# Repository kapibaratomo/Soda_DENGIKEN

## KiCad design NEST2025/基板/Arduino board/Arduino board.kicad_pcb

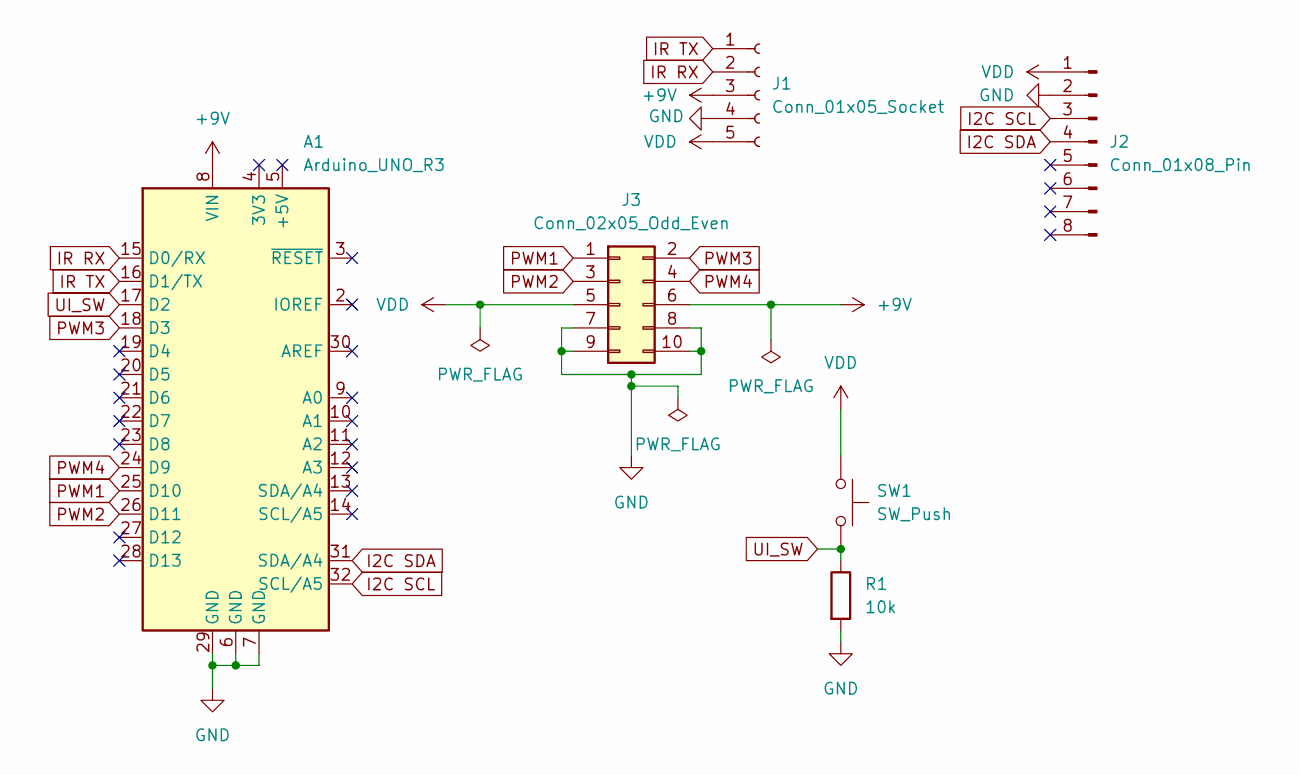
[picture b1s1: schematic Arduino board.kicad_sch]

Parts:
A1: Arduino_UNO_R3
J1: Conn_01x05_Socket; JST_XH_B5B-XH-A_1x05_P2.50mm_Vertical
J2: Conn_01x08_Pin; PinSocket_1x08_P2.54mm_Vertical
J3: Conn_02x05_Odd_Even; IDC-Header_2x05_P2.54mm_Vertical
R1: 10k; R_0603_1608Metric
SW1: SW_Push; TVGP01-G73BB

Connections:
+9V: A1.8 (VIN), J1.3, J3.6
GND: A1.6 (GND), A1.7 (GND), A1.29 (GND), J1.4, J2.2, J3.7, J3.8, J3.9, J3.10, R1.2
I2C SCL: A1.32 (SCL/A5), J2.3
I2C SDA: A1.31 (SDA/A4), J2.4
IR RX: A1.15 (D0/RX), J1.2
IR TX: A1.16 (D1/TX), J1.1
PWM1: A1.25 (D10), J3.1
PWM2: A1.26 (D11), J3.3
PWM3: A1.18 (D3), J3.2
PWM4: A1.24 (D9), J3.4
UI_SW: A1.17 (D2), R1.1, SW1.2
VDD: J1.5, J2.1, J3.5, SW1.1

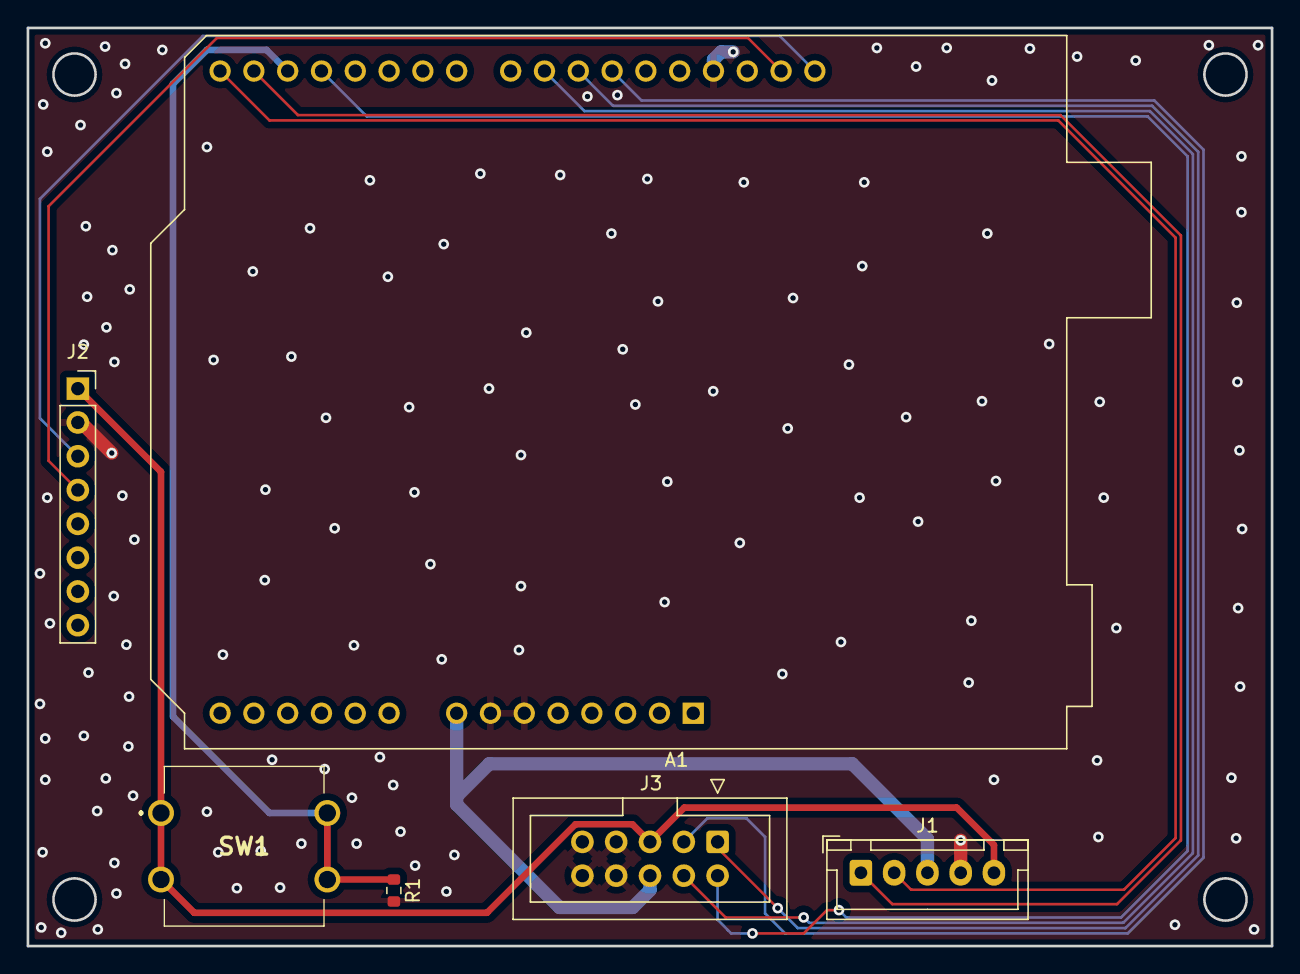
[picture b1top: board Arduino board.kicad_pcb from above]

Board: 2 copper layers, 93.5 x 69.0 mm, 6 parts (0 on the bottom side), 12 nets.

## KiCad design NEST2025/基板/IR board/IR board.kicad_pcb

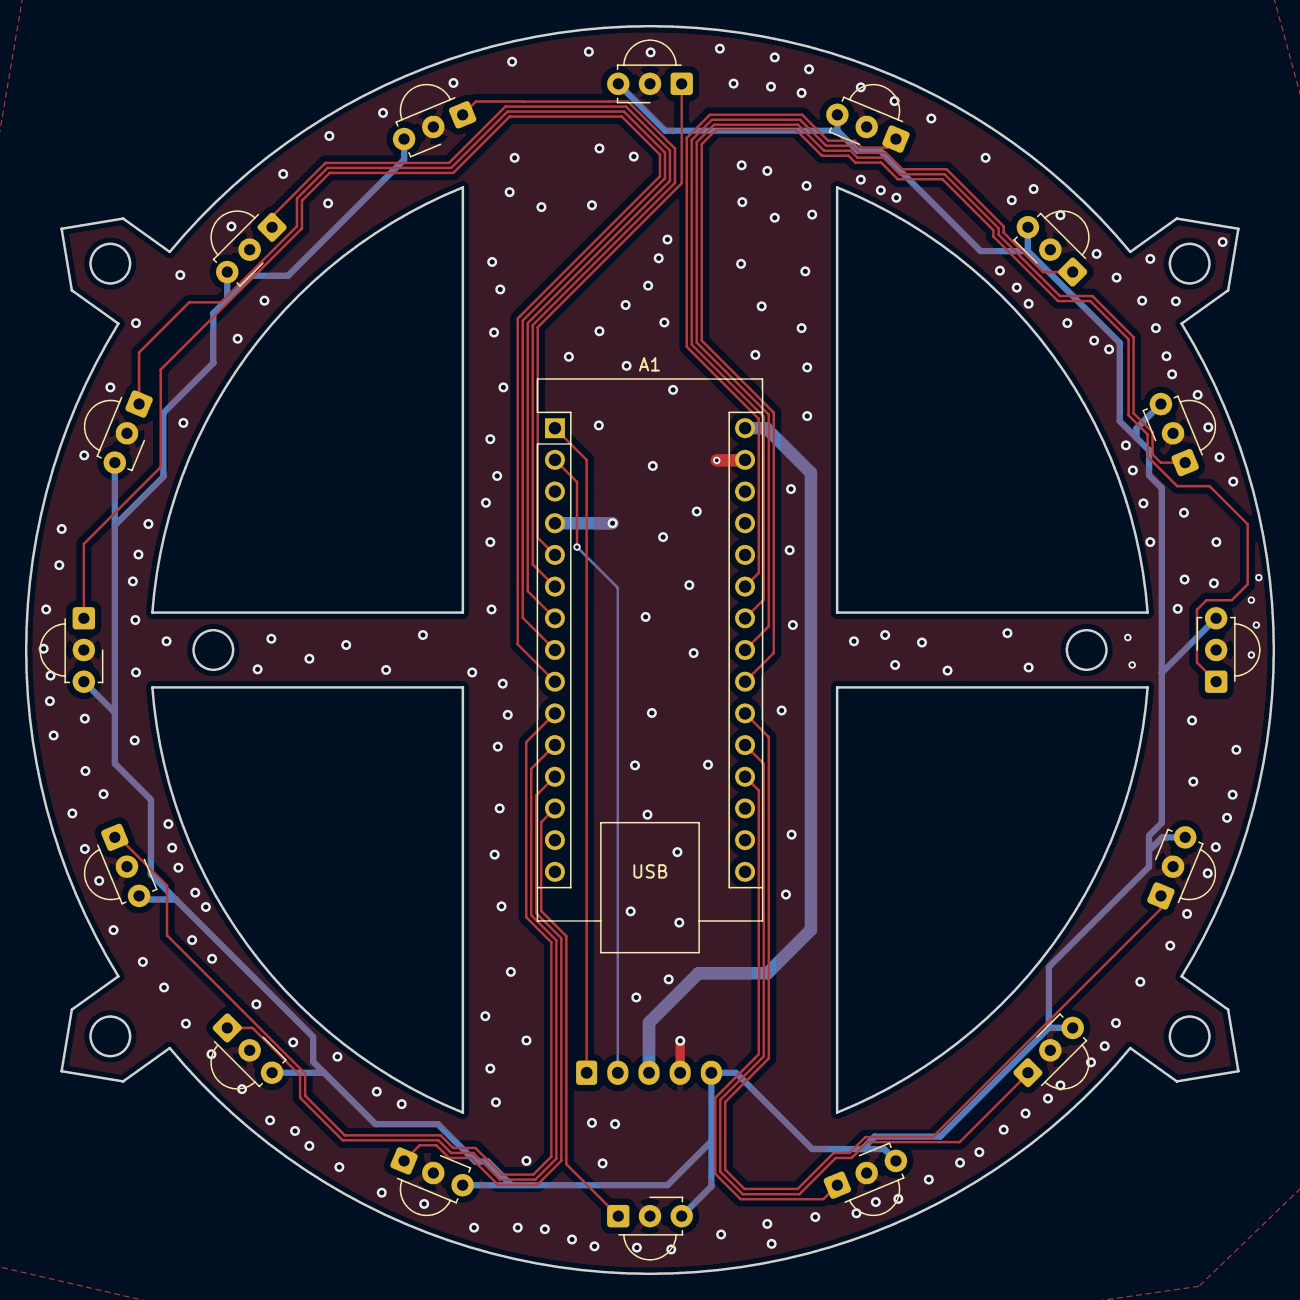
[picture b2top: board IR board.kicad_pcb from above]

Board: 2 copper layers, 100.0 x 100.0 mm, 18 parts (1 on the bottom side), 21 nets.

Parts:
A1: Arduino_Nano_Every; Arduino_Nano
J1: Conn_01x05_Socket; JST_XH_B5B-XH-A_1x05_P2.50mm_Vertical
U1, U2, U3, U4, U5, U6, U7, U8, U9, U10, U11, U12, U13, U14, U15, U16: TSSP58038; Vishay_MINICAST-3Pin

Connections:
+3.3V: J1.5, U1.3 (Vs), U2.3 (Vs), U3.3 (Vs), U4.3 (Vs), U5.3 (Vs), U6.3 (Vs), U7.3 (Vs), U8.3 (Vs), U9.3 (Vs), U10.3 (Vs), U11.3 (Vs), U12.3 (Vs), U13.3 (Vs), U14.3 (Vs), U15.3 (Vs), U16.3 (Vs)
+9V: A1.30 (VIN), J1.3
GND: A1.4 (GND), A1.29 (GND), J1.4, U1.2 (GND), U2.2 (GND), U3.2 (GND), U4.2 (GND), U5.2 (GND), U6.2 (GND), U7.2 (GND), U8.2 (GND), U9.2 (GND), U10.2 (GND), U11.2 (GND), U12.2 (GND), U13.2 (GND), U14.2 (GND), U15.2 (GND), U16.2 (GND)
IR 0: A1.5 (D2), U1.1 (OUT)
IR 1: A1.6 (D3), U2.1 (OUT)
IR 2: A1.7 (D4), U3.1 (OUT)
IR 3: A1.8 (D5), U4.1 (OUT)
IR 4: A1.9 (D6), U5.1 (OUT)
IR 5: A1.10 (D7), U6.1 (OUT)
IR 6: A1.11 (D8), U7.1 (OUT)
IR 7: A1.12 (D9), U8.1 (OUT)
IR 8: A1.13 (D10), U9.1 (OUT)
IR 9: A1.19 (A0), U10.1 (OUT)
IR 10: A1.20 (A1), U11.1 (OUT)
IR 11: A1.21 (A2), U12.1 (OUT)
IR 12: A1.22 (A3), U13.1 (OUT)
IR 13: A1.23 (SDA/A4), U14.1 (OUT)
IR 14: A1.24 (SCL/A5), U15.1 (OUT)
IR 15: A1.25 (A6), U16.1 (OUT)
IR RX: A1.2 (RX1), J1.2
IR TX: A1.1 (TX1), J1.1

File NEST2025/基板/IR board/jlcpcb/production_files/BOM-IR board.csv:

Comment,Designator,Footprint,LCSC,Quantity
TSSP58038,U15,Vishay_MINICAST-3Pin,,1
TSSP58038,U9,Vishay_MINICAST-3Pin,,1
TSSP58038,U13,Vishay_MINICAST-3Pin,,1
TSSP58038,U5,Vishay_MINICAST-3Pin,,1
TSSP58038,U8,Vishay_MINICAST-3Pin,,1
TSSP58038,U6,Vishay_MINICAST-3Pin,,1
TSSP58038,U14,Vishay_MINICAST-3Pin,,1
TSSP58038,U16,Vishay_MINICAST-3Pin,,1
TSSP58038,U1,Vishay_MINICAST-3Pin,,1
TSSP58038,U12,Vishay_MINICAST-3Pin,,1
TSSP58038,U10,Vishay_MINICAST-3Pin,,1
TSSP58038,U11,Vishay_MINICAST-3Pin,,1
TSSP58038,U2,Vishay_MINICAST-3Pin,,1
TSSP58038,U7,Vishay_MINICAST-3Pin,,1
TSSP58038,U4,Vishay_MINICAST-3Pin,,1
Arduino_Nano_Every,A1,Arduino_Nano,,1
TSSP58038,U3,Vishay_MINICAST-3Pin,,1
Conn_01x05_Socket,J1,JST_XH_B5B-XH-A_1x05_P2.50mm_Vertical,,1

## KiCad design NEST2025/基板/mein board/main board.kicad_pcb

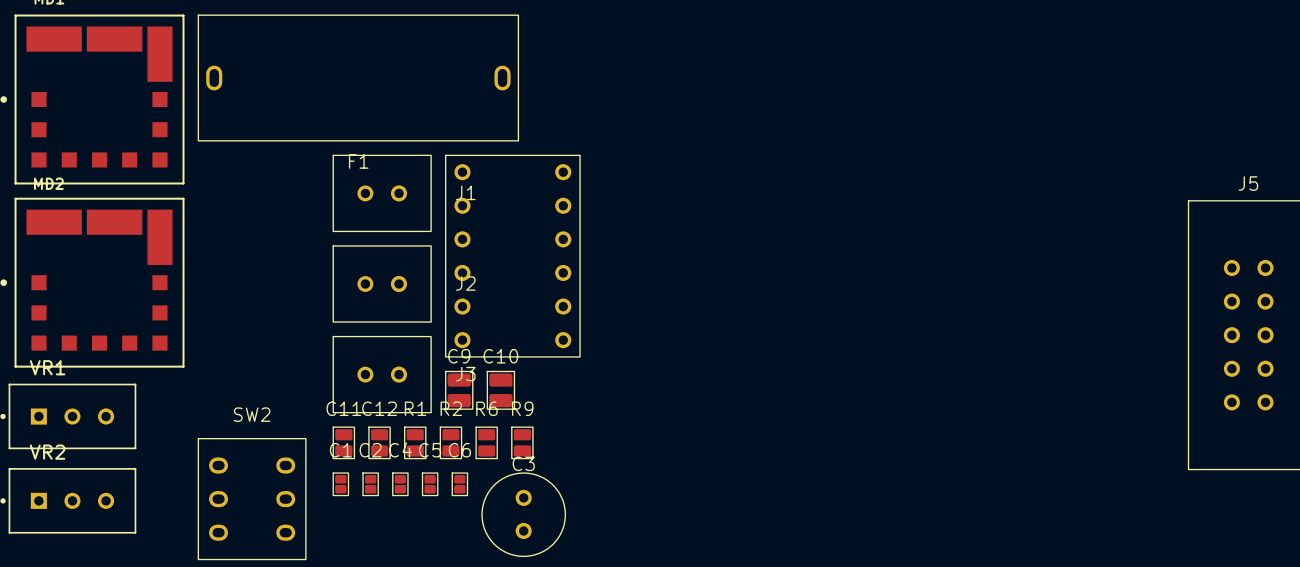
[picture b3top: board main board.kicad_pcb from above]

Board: 2 copper layers, 25 parts (0 on the bottom side), 19 nets, no tracks yet.

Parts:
C1, C2, C4, C6: 0.1; chip 1005
C3: 100; OS-CON 100μF
C5: 1; chip 1005
C9, C10: 22; chip 2012
C11, C12: 10; chip 1608
F1: Fuse
J1, J2, J3: Conn_01x02_Socket; XHConn_01×02_Socket
J5: Conn_02x05_Odd_Even; Box header 10P
MD1: OKL-T_3-W5N-C; OKL-T-3-W5N-C_0
MD2: OKL-T_6-W12N-C; OKL-T-6-W12N-C_0
R1, R2, R6, R9: 1.2k; chip 1608
SW2: SW_Push_DPDT; 6P toggle switch
U1: DRV8835
VR1, VR2: 3296W-1-203LF

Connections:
+3.3V: C11.1, C12.1, J5.5, MD1.4 (VOUT), MD1.5 (SENSE), MD2.4 (VOUT), MD2.5 (SENSE), R1.1, R9.1
+5V: C5.1, C6.1, J5.6, U1.7 (VDD)
+9V: C3.2, C4.2, C9.1, C10.1, MD1.2 (VIN), MD2.2 (VIN), SW2.1 (A), SW2.4 (A), U1.1 (VM)
AOUT1: C1.1, J1.1, U1.2 (AOUT1)
AOUT2: C1.2, J1.2, U1.3 (AOUT2)
BOUT1: C2.1, J2.1, U1.4 (BOUT1)
BOUT2: C2.2, J2.2, U1.5 (BOUT2)
GND: C3.1, C4.1, C9.2, C10.2, C11.2, C12.2, J3.1, J5.7, J5.8, J5.9, J5.10, MD1.1 (~ON/OFF_CONTROL), MD1.3 (1_GROUND), MD1.7 (2_GROUND), MD2.1 (~ON/OFF_CONTROL), MD2.3 (1_GROUND), MD2.7 (2_GROUND), R1.2, R2.2, R6.2, R9.2, U1.6 (GND)
unnamed: F1.2, SW2.2 (B), SW2.5 (B)
unnamed: F1.1, J3.2
unnamed: MD1.6 (TRIM), VR1.1
unnamed: MD2.6 (TRIM), VR2.1
unnamed: R2.1, VR2.2, VR2.3
unnamed: R6.1, VR1.2, VR1.3
unnamed: C5.2, C6.2, U1.8 (MODE)
PWM1: J5.1, U1.9 (AIN1)
PWM2: J5.3, U1.10 (AIN2)
PWM3: J5.2, U1.11 (BIN1)
PWM4: J5.4, U1.12 (BIN2)

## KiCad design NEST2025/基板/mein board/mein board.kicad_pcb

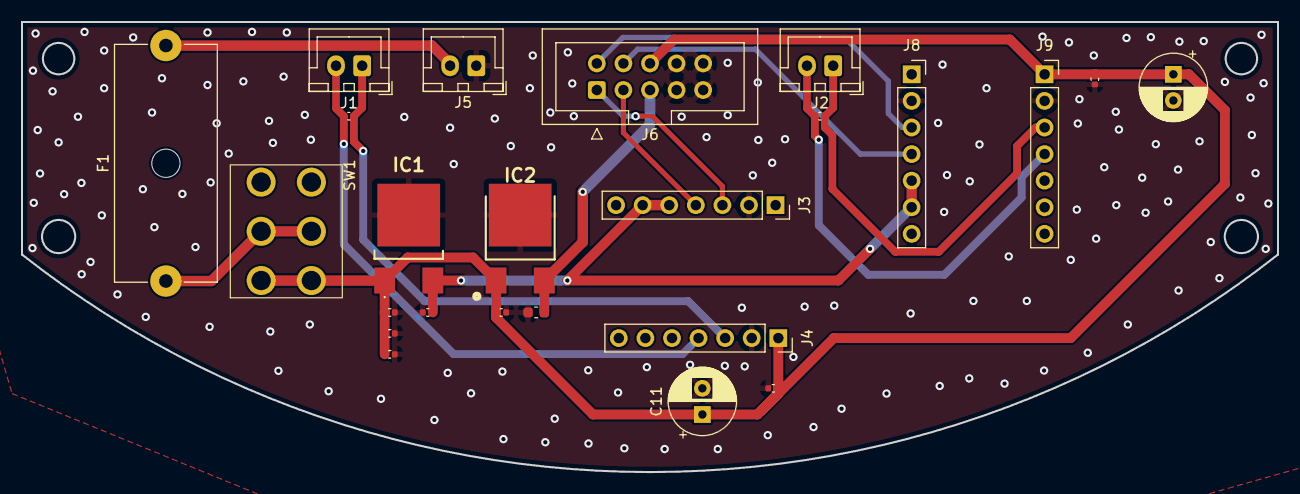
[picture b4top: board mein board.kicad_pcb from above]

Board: 2 copper layers, 120.0 x 43.0 mm, 24 parts (0 on the bottom side), 14 nets.

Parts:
C1, C2, C3, C4, C5: 0.1uF; C_0402_1005Metric
C6: 10uF; C_0603_1608Metric
C7, C8, C10, C12: 0.1; C_0402_1005Metric
C9, C11: 100; CP_Radial_D6.3mm_P2.50mm
F1: Fuse; Fuseholder_Cylinder-5x20mm_Schurter_0031_8201_Horizontal_Op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
IC1: NJM7805SDL1-TE1; NJM7805SDL1TE1
IC2: NJM2391DL1-33-TE1
J1, J2, J5: Conn_01x02_Socket; JST_XH_B2B-XH-A_1x02_P2.50mm_Vertical
J3, J4, J8, J9: Conn_01x07_Pin; PinSocket_1x07_P2.54mm_Vertical
J6: Conn_02x05_Odd_Even; IDC-Header_2x05_P2.54mm_Vertical
SW1: SW_Push_DPDT; Toggle

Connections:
+3.3V: C6.1, IC2.2 (VOUT), J6.5
+5V: C4.1, IC1.3 (VOUT), J3.5, J3.6, J8.5, J8.6
+9V: C1.1, C2.1, C3.1, C5.1, C9.1, C10.1, C11.1, C12.1, IC1.1 (VIN), IC2.1 (VIN), J4.1, J6.6, J9.1, SW1.1 (A), SW1.4 (A)
AOUT1: C7.1, J1.1, J4.3
AOUT2: C7.2, J1.2, J4.4
BOUT1: C8.1, J2.1, J9.3
BOUT2: C8.2, J2.2, J9.4
GND: C1.2, C2.2, C3.2, C4.2, C5.2, C6.2, C9.2, C10.2, C11.2, C12.2, IC1.2 (GND), IC2.3 (GND), J3.2, J4.2, J5.1, J6.7, J6.8, J6.9, J6.10, J8.2, J9.2
unnamed: F1.2, SW1.2 (B), SW1.5 (B)
unnamed: F1.1, J5.2
PWM1: J3.3, J6.1
PWM2: J3.4, J6.3
PWM3: J6.2, J8.3
PWM4: J6.4, J8.4

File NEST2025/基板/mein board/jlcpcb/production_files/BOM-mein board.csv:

Comment,Designator,Footprint,LCSC,Quantity
0.1uF,C3,C_0402_1005Metric,,1
0.1uF,C4,C_0402_1005Metric,,1
Fuse,F1,Fuseholder_Cylinder-5x20mm_Schurter_0031_8201_Horizontal_Open,,1
0.1uF,C2,C_0402_1005Metric,,1
0.1,C7,C_0402_1005Metric,,1
0.1,C10,C_0402_1005Metric,,1
Conn_01x07_Pin,J4,PinSocket_1x07_P2.54mm_Vertical,,1
Conn_01x02_Socket,J1,JST_XH_B2B-XH-A_1x02_P2.50mm_Vertical,,1
Conn_01x07_Pin,J3,PinSocket_1x07_P2.54mm_Vertical,,1
10uF,C6,C_0603_1608Metric,,1
100,C9,CP_Radial_D6.3mm_P2.50mm,,1
0.1uF,C5,C_0402_1005Metric,,1
100,C11,CP_Radial_D6.3mm_P2.50mm,,1
Conn_01x02_Socket,J2,JST_XH_B2B-XH-A_1x02_P2.50mm_Vertical,,1
0.1uF,C1,C_0402_1005Metric,,1
NJM2391DL1-33-TE1,IC2,NJM2391DL1-33-TE1,,1
SW_Push_DPDT,SW1,Toggle,,1
0.1,C12,C_0402_1005Metric,,1
NJM7805SDL1-TE1,IC1,NJM7805SDL1TE1,,1
0.1,C8,C_0402_1005Metric,,1
Conn_02x05_Odd_Even,J6,IDC-Header_2x05_P2.54mm_Vertical,,1
Conn_01x07_Pin,J9,PinSocket_1x07_P2.54mm_Vertical,,1
Conn_01x02_Socket,J5,JST_XH_B2B-XH-A_1x02_P2.50mm_Vertical,,1
Conn_01x07_Pin,J8,PinSocket_1x07_P2.54mm_Vertical,,1

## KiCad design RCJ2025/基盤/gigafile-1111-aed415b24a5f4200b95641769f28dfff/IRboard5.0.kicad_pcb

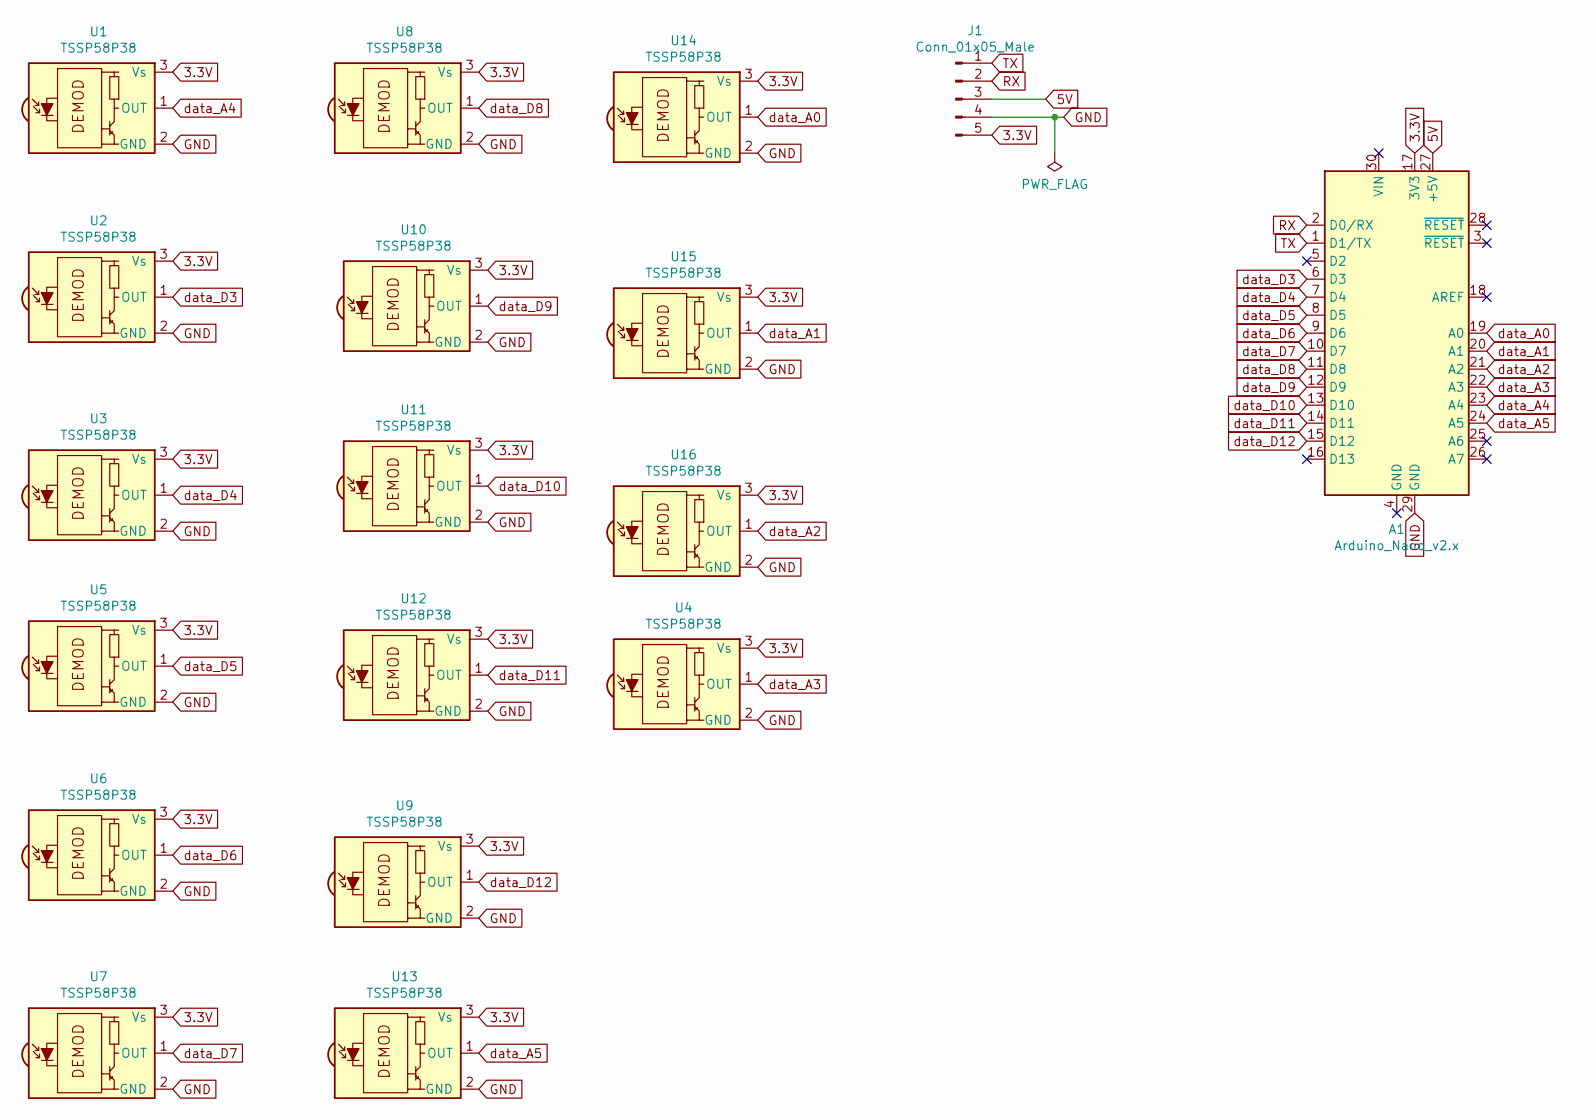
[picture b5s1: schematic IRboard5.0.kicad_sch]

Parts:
A1: Arduino_Nano_v2.x; Arduino_Nano
J1: Conn_01x05_Male; JST_XH_B5B-XH-A_1x05_P2.50mm_Vertical
U1, U2, U3, U4, U5, U6, U7, U8, U9, U10, U11, U12, U13, U14, U15, U16: TSSP58P38; Vishay_MINICAST-3Pin

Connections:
3.3V: A1.17 (3V3), J1.5, U1.3 (Vs), U2.3 (Vs), U3.3 (Vs), U4.3 (Vs), U5.3 (Vs), U6.3 (Vs), U7.3 (Vs), U8.3 (Vs), U9.3 (Vs), U10.3 (Vs), U11.3 (Vs), U12.3 (Vs), U13.3 (Vs), U14.3 (Vs), U15.3 (Vs), U16.3 (Vs)
5V: A1.27 (+5V), J1.3
GND: A1.29 (GND), J1.4, U1.2 (GND), U2.2 (GND), U3.2 (GND), U4.2 (GND), U5.2 (GND), U6.2 (GND), U7.2 (GND), U8.2 (GND), U9.2 (GND), U10.2 (GND), U11.2 (GND), U12.2 (GND), U13.2 (GND), U14.2 (GND), U15.2 (GND), U16.2 (GND)
RX: A1.2 (D0/RX), J1.2
TX: A1.1 (D1/TX), J1.1
data_A0: A1.19 (A0), U14.1 (OUT)
data_A1: A1.20 (A1), U15.1 (OUT)
data_A2: A1.21 (A2), U16.1 (OUT)
data_A3: A1.22 (A3), U4.1 (OUT)
data_A4: A1.23 (A4), U1.1 (OUT)
data_A5: A1.24 (A5), U13.1 (OUT)
data_D3: A1.6 (D3), U2.1 (OUT)
data_D4: A1.7 (D4), U3.1 (OUT)
data_D5: A1.8 (D5), U5.1 (OUT)
data_D6: A1.9 (D6), U6.1 (OUT)
data_D7: A1.10 (D7), U7.1 (OUT)
data_D8: A1.11 (D8), U8.1 (OUT)
data_D9: A1.12 (D9), U10.1 (OUT)
data_D10: A1.13 (D10), U11.1 (OUT)
data_D11: A1.14 (D11), U12.1 (OUT)
data_D12: A1.15 (D12), U9.1 (OUT)

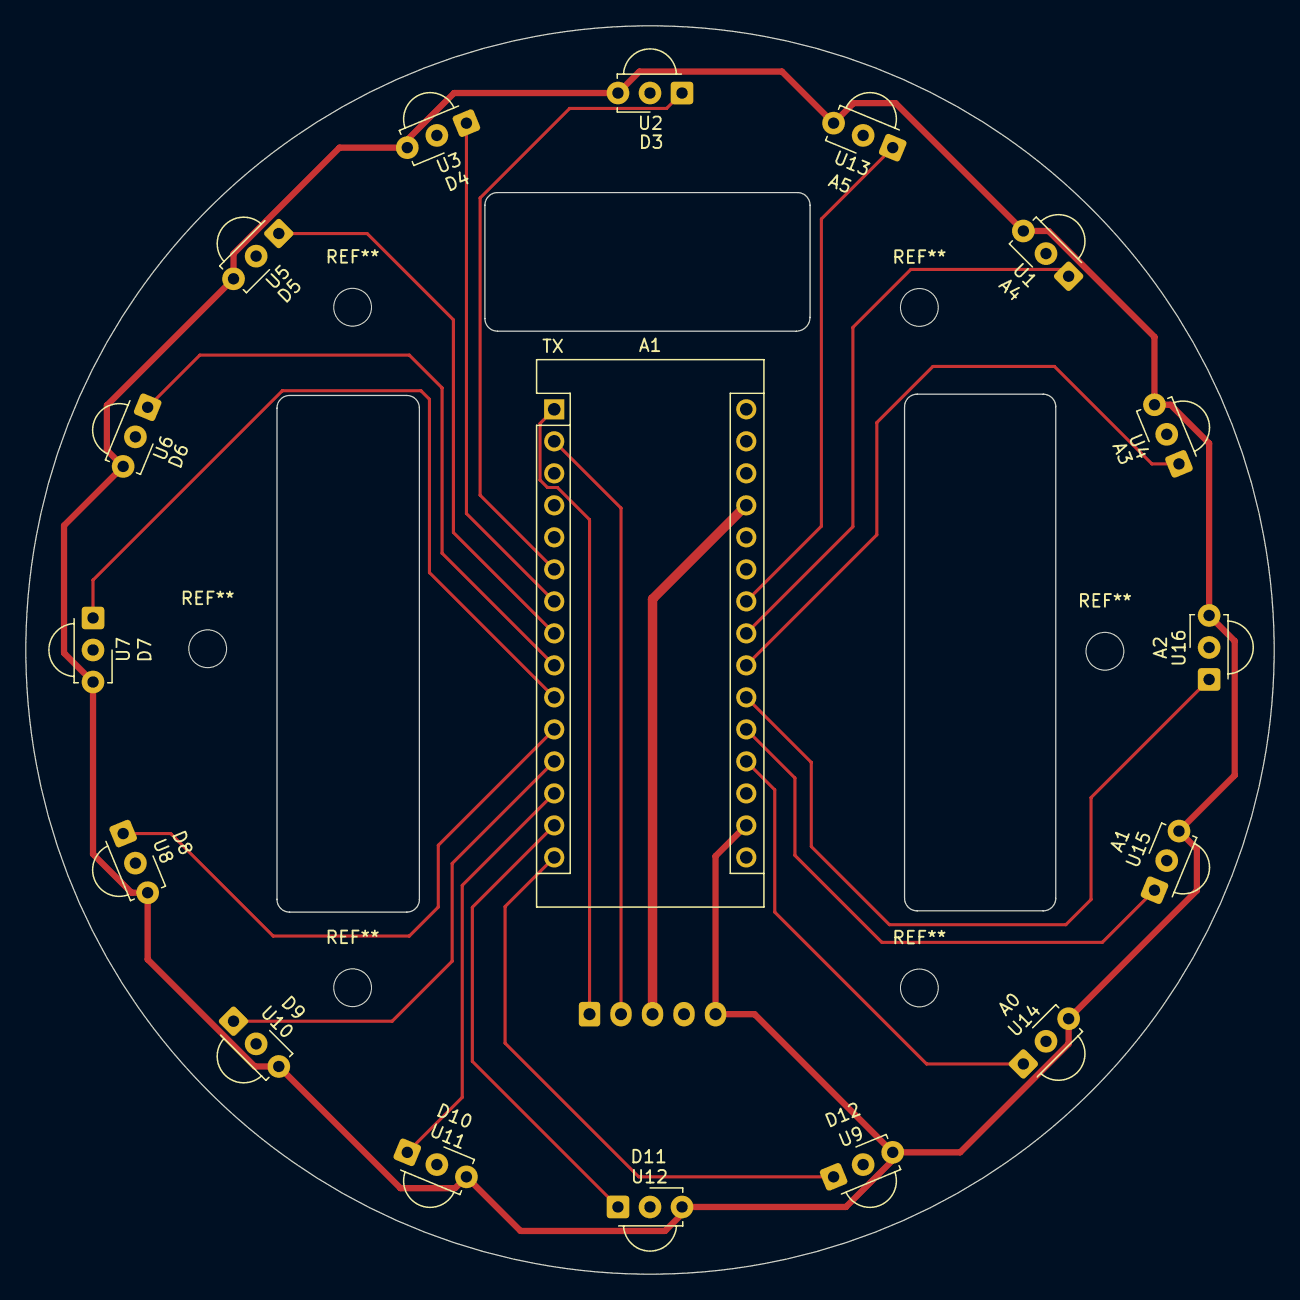
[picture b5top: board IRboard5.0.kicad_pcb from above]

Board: 2 copper layers, 99.1 x 99.1 mm, 18 parts (1 on the bottom side), 21 nets.

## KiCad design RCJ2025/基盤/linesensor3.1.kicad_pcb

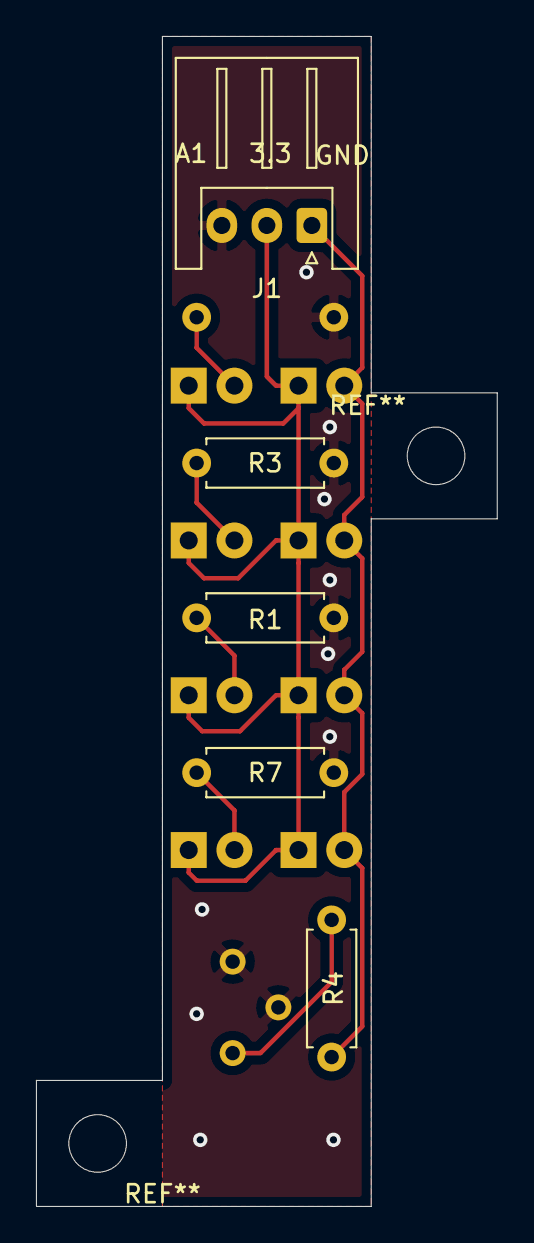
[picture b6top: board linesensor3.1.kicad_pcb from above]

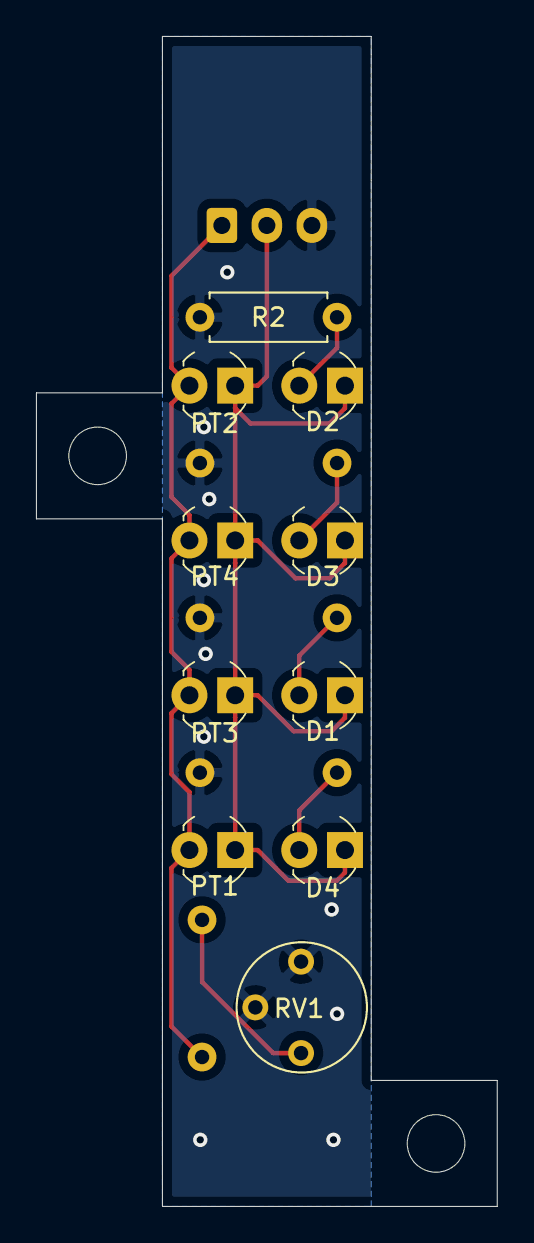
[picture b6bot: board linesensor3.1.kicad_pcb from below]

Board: 2 copper layers, 25.6 x 65.0 mm, 15 parts (10 on the bottom side), 8 nets.

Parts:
D1, D2, D3, D4: LED; LED_3mm_Radial
J1: Conn_01x03_Female; JST_XH_S3B-XH-A_1x03_P2.50mm_Horizontal
PT1, PT2, PT3, PT4: NJL7302L-F3; LED_3mm_Radial
R1, R2, R3, R4, R7: R; R_Axial_DIN0207_L6.3mm_D2.5mm_P7.62mm_Horizontal
RV1: R_POT; Potentiometer_Vishay_T7-YA_Single_Vertical

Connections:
+3V3: D1.1, D2.1, D3.1, D4.1, J1.2, PT1.1, PT2.1, PT3.1, PT4.1
A1: J1.1, PT1.2, PT2.2, PT3.2, PT4.2, R4.1
GND: J1.3, R1.2, R2.2, R3.2, R7.2, RV1.1, RV1.2
unnamed: D1.2, R1.1
unnamed: D2.2, R2.1
unnamed: D3.2, R3.1
unnamed: D4.2, R7.1
unnamed: R4.2, RV1.3

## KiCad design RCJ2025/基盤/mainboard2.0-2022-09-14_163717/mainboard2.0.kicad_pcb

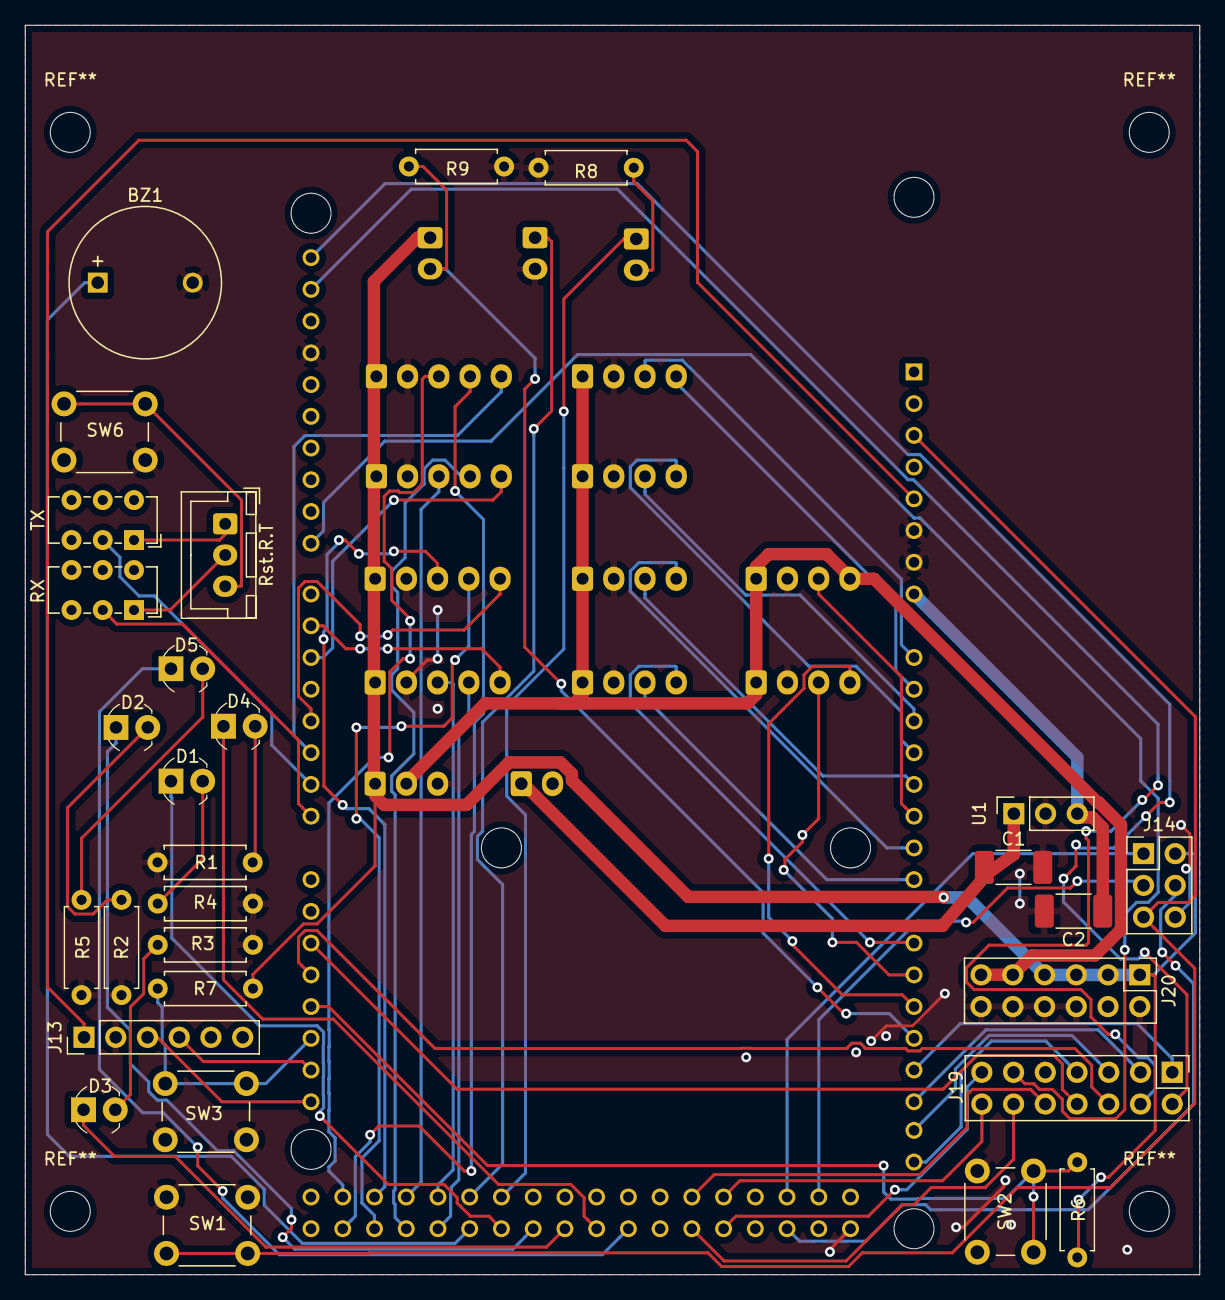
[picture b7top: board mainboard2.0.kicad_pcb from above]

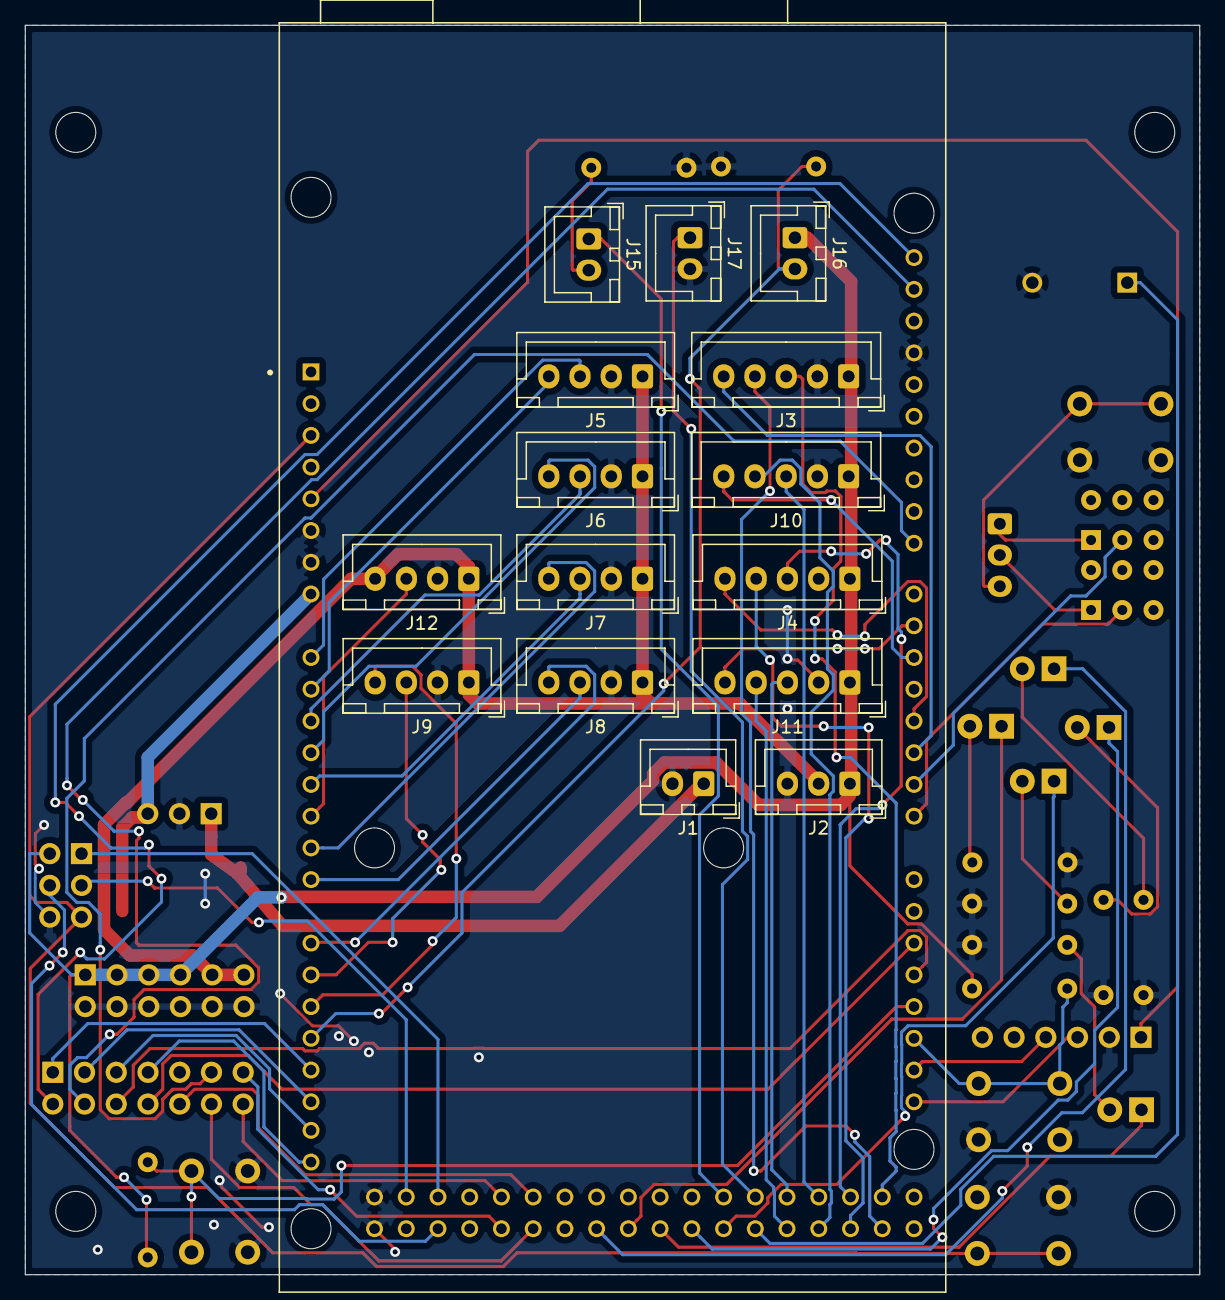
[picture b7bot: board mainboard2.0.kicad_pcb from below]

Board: 2 copper layers, 94.0 x 100.0 mm, 45 parts (16 on the bottom side), 71 nets.

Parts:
A1: ARDUINO_MEGA2560_REV3_-_RETAIL
BZ1: Buzzer; MagneticBuzzer_ProSignal_ABI-009-RC
C1, C2: C; C_2010_5025Metric_Pad1.52x2.65mm_HandSolder
D1, D2, D3, D4, D5: LED; LED_3mm_Radial
J1, J15, J16, J17: Conn_01x02_Male; JST_XH_B2B-XH-A_1x02_P2.50mm_Vertical
J2: Conn_01x03_Male; JST_XH_B3B-XH-A_1x03_P2.50mm_Vertical
J3, J4, J10, J11: Conn_01x05_Male; JST_XH_B5B-XH-A_1x05_P2.50mm_Vertical
J5, J6, J7, J8, J9, J12: Conn_01x04_Male; JST_XH_B4B-XH-A_1x04_P2.50mm_Vertical
J13: Conn_01x06_Male; PinHeader_1x06_P2.54mm_Vertical
J14: Conn_02x03_Odd_Even; PinHeader_2x03_P2.54mm_Vertical
J19: Conn_02x07_Odd_Even; PinHeader_2x07_P2.54mm_Vertical
J20: Conn_02x06_Odd_Even; PinHeader_2x06_P2.54mm_Vertical
R1, R2, R3, R4, R5, R6, R7, R8, R9: R; R_Axial_DIN0207_L6.3mm_D2.5mm_P7.62mm_Horizontal
RX: SLIDE_SWITCH_2-3; SW_E-Switch_EG1271_DPDT
Rst.R.T: Conn_01x03_Male; JST_XH_B3B-XH-A_1x03_P2.50mm_Vertical
SW1: SW_Push; SW_PUSH_6mm
SW2, SW3, SW6: SW_Push_Dual; SW_PUSH_6mm
TX: SLIDE_SWITCH_2-3; SW_E-Switch_EG1271_DPDT
U1: NJM2391DL1; PinSocket_1x03_P2.54mm_Vertical

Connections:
44: A1.44, J19.10
45: A1.45, J19.12
46: A1.46, J19.14
47.: A1.47, J19.13
+3V3: J2.2, J5.1, J6.1, J7.1, J8.1, J9.1, J12.1, J12.4, J20.9, J20.11
+5V: J2.1, J3.1, J4.1, J10.1, J11.1, J14.2, J16.1, J20.1, J20.3, J20.5, J20.7, R6.2, R7.2
+12V: C1.1, J1.1, U1.VI
A12: A1.AD12, J19.1
A13: A1.AD13, J19.3
A14: A1.AD14, J19.5
A15: A1.AD15, J19.7
GND: A1.GND1, A1.GND2, A1.GND3, A1.GND4, A1.GND5, BZ1.2, C1.2, C2.2, J1.2, J2.3, J3.2, J4.2, J5.2, J6.2, J7.2, J8.2, J9.2, J10.2, J11.2, J12.2, J13.2, J14.6, J17.2, J20.2, J20.4, J20.6, J20.8, J20.10, J20.12, R1.2, R2.2, R3.2, R4.2, R5.2, R8.2, R9.2, SW1.1, SW2.2, SW2.4, SW3.2, SW3.4, SW6.1, SW6.3, U1.GND
IR_dis: A1.AD5, J12.3
LED1: A1.33, D1.1
LED2: A1.35, D2.1
LED3: A1.37, D3.1
LED4: A1.39, D4.1
LED5: A1.41, D5.1
LED_ball: A1.32, J15.1
LINE_1: A1.AD0, J5.3
LINE_2: A1.AD1, J5.4
LINE_3: A1.AD2, J6.3
LINE_4: A1.AD3, J6.4
LINE_5: A1.AD4, J7.3
LINE_6: A1.AD6, J7.4
LINE_7: A1.AD7, J8.3
LINE_8: A1.AD8, J8.4
LINE_9: A1.AD9, J9.3
LINE_10: A1.AD10, J9.4
MISO: A1.50, J14.1
MOSI: A1.51, J14.4
MPU_RST: A1.19, R7.1, SW3.1, SW3.3
Motor1_A: A1.22, J3.3
Motor1_B: A1.23, J3.4
Motor1_PWM: A1.2, J3.5
Motor2_A: A1.24, J4.3
Motor2_B: A1.25, J4.4
Motor2_PWM: A1.3, J4.5
Motor3_A: A1.26, J10.3
Motor3_B: A1.27, J10.4
Motor3_PWM: A1.5, J10.5
Motor4_A: A1.28, J11.3
Motor4_B: A1.29, J11.4
Motor4_PWM: A1.6, J11.5
unnamed: A1.5V_1, J13.1
unnamed: A1.31, BZ1.1
unnamed: A1.VIN, C2.1, U1.VO
unnamed: D1.2, R1.1
unnamed: D2.2, R2.1
unnamed: D3.2, R3.1
unnamed: D4.2, R4.1
unnamed: D5.2, R5.1
unnamed: J15.2, R8.1
unnamed: Rst.R.T.1, TX.1
unnamed: RX.1, Rst.R.T.2
unnamed: Rst.R.T.3, SW6.2, SW6.4
PWM_7: A1.7, J19.9
PWM_8: A1.8, J19.11
RESET: A1.RESET, J14.5, SW1.2
RX: A1.0, RX.2
RX1: A1.17, J19.6
SCK: A1.52, J14.3
SCL: A1.SCL, J19.2
SCL_MPU: A1.21, J13.3
SDA: A1.SDA, J19.4
SDA_MPU: A1.20, J13.4
SW: A1.18, R6.1, SW2.1, SW2.3
TX: A1.1, TX.2
TX1: A1.16, J19.8
ball_sen: A1.AD11, J16.2, R9.1
kicker: A1.30, J17.1

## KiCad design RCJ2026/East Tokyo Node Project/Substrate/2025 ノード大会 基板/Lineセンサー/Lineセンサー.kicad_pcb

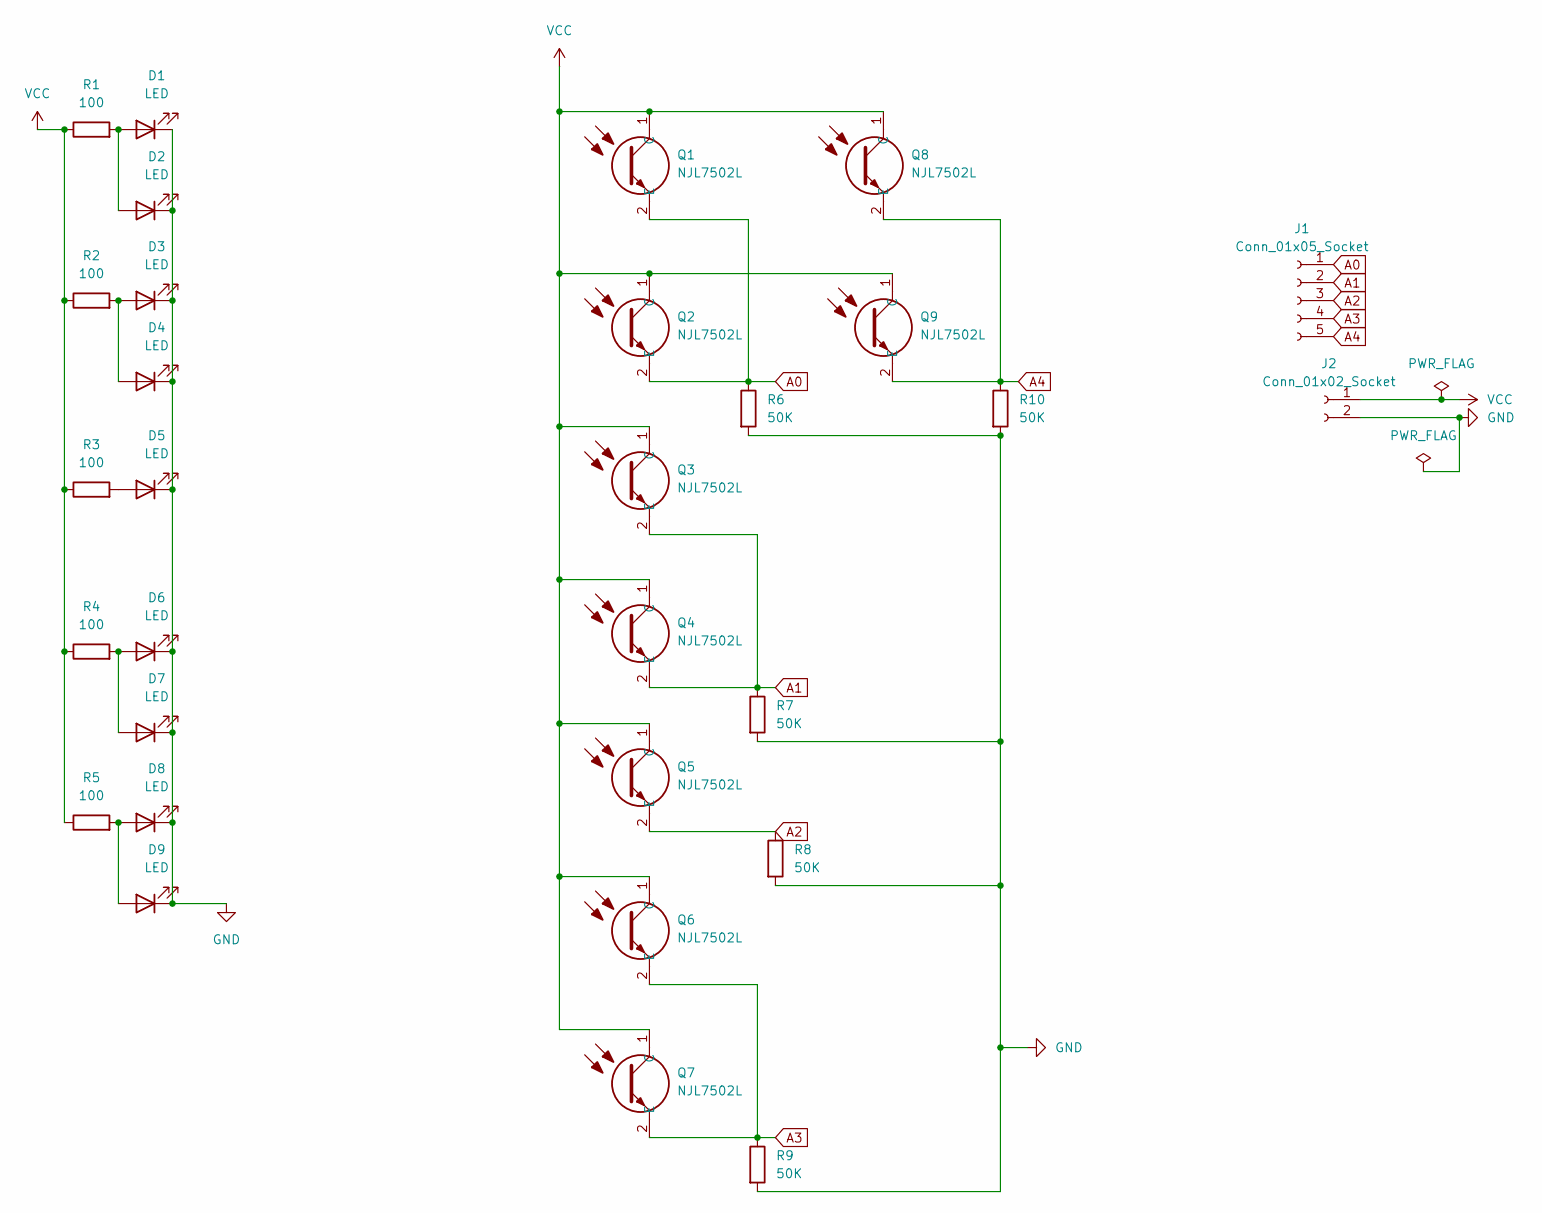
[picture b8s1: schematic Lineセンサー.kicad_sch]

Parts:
D1, D2, D3, D4, D5, D6, D7, D8, D9: LED; LED_D5.0mm_Clear
J1: Conn_01x05_Socket; JST_XH_B5B-XH-A_1x05_P2.50mm_Vertical
J2: Conn_01x02_Socket; JST_XH_B2B-XH-A_1x02_P2.50mm_Vertical
Q1, Q2, Q3, Q4, Q5, Q6, Q7, Q8, Q9: NJL7502L
R1, R2, R3, R4, R5: 100; R_0603_1608Metric
R6, R7, R8, R9, R10: 50K; R_0603_1608Metric

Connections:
A0: J1.1, Q1.2 (E), Q2.2 (E), R6.1
A1: J1.2, Q3.2 (E), Q4.2 (E), R7.1
A2: J1.3, Q5.2 (E), R8.1
A3: J1.4, Q6.2 (E), Q7.2 (E), R9.1
A4: J1.5, Q8.2 (E), Q9.2 (E), R10.1
GND: D1.1 (K), D2.1 (K), D3.1 (K), D4.1 (K), D5.1 (K), D6.1 (K), D7.1 (K), D8.1 (K), D9.1 (K), J2.2, R6.2, R7.2, R8.2, R9.2, R10.2
unnamed: D1.2 (A), D2.2 (A), R1.2
unnamed: D3.2 (A), D4.2 (A), R2.2
unnamed: D5.2 (A), R3.2
unnamed: D6.2 (A), D7.2 (A), R4.2
unnamed: D8.2 (A), D9.2 (A), R5.2
VCC: J2.1, Q1.1 (C), Q2.1 (C), Q3.1 (C), Q4.1 (C), Q5.1 (C), Q6.1 (C), Q7.1 (C), Q8.1 (C), Q9.1 (C), R1.1, R2.1, R3.1, R4.1, R5.1
